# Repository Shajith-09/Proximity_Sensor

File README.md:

View this project on [CADLAB.io](https://cadlab.io/project/29333). 

# Proximity_Sensor

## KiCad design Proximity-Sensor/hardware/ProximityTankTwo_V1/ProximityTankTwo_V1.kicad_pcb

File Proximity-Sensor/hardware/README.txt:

cristinel.ababei, 2020

These are KiCad complete projects for:

--Base board
ProximityMother_V1/

--Single LC tank, 7 turns
ProximityTankOne_Square7Turns/

--Dual LC tank, 14 turns each
ProximityTankTwo_V1/

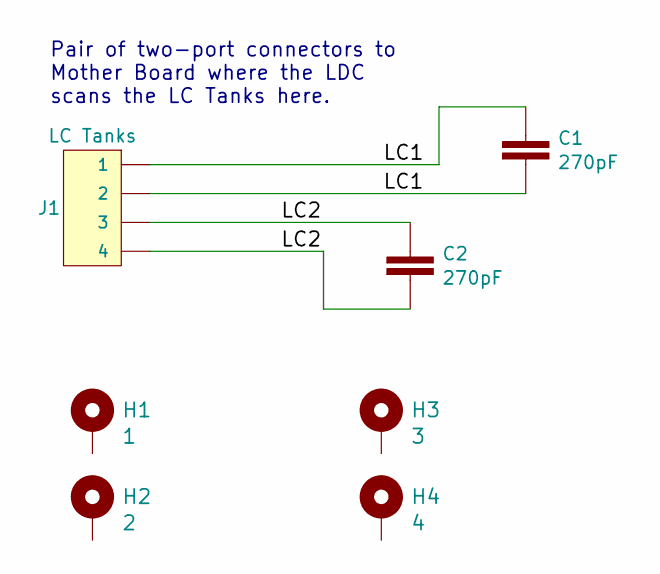
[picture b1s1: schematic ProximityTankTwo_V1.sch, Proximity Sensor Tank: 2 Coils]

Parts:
C1, C2: 270pF; C_0805_2012Metric_Pad1.15x1.40mm_HandSolder
H1: 1; STANDOFF_GROUNDING
H2: 2; STANDOFF_GROUNDING
H3: 3; STANDOFF_GROUNDING
H4: 4; STANDOFF_GROUNDING
J1: LC Tanks; 1X04

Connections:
/LC1: C1.1, C1.2, J1.1, J1.2
/LC2: C2.1, C2.2, J1.3, J1.4

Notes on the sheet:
Pair of two-port connectors to Mother Board where the LDC scans the LC Tanks here.

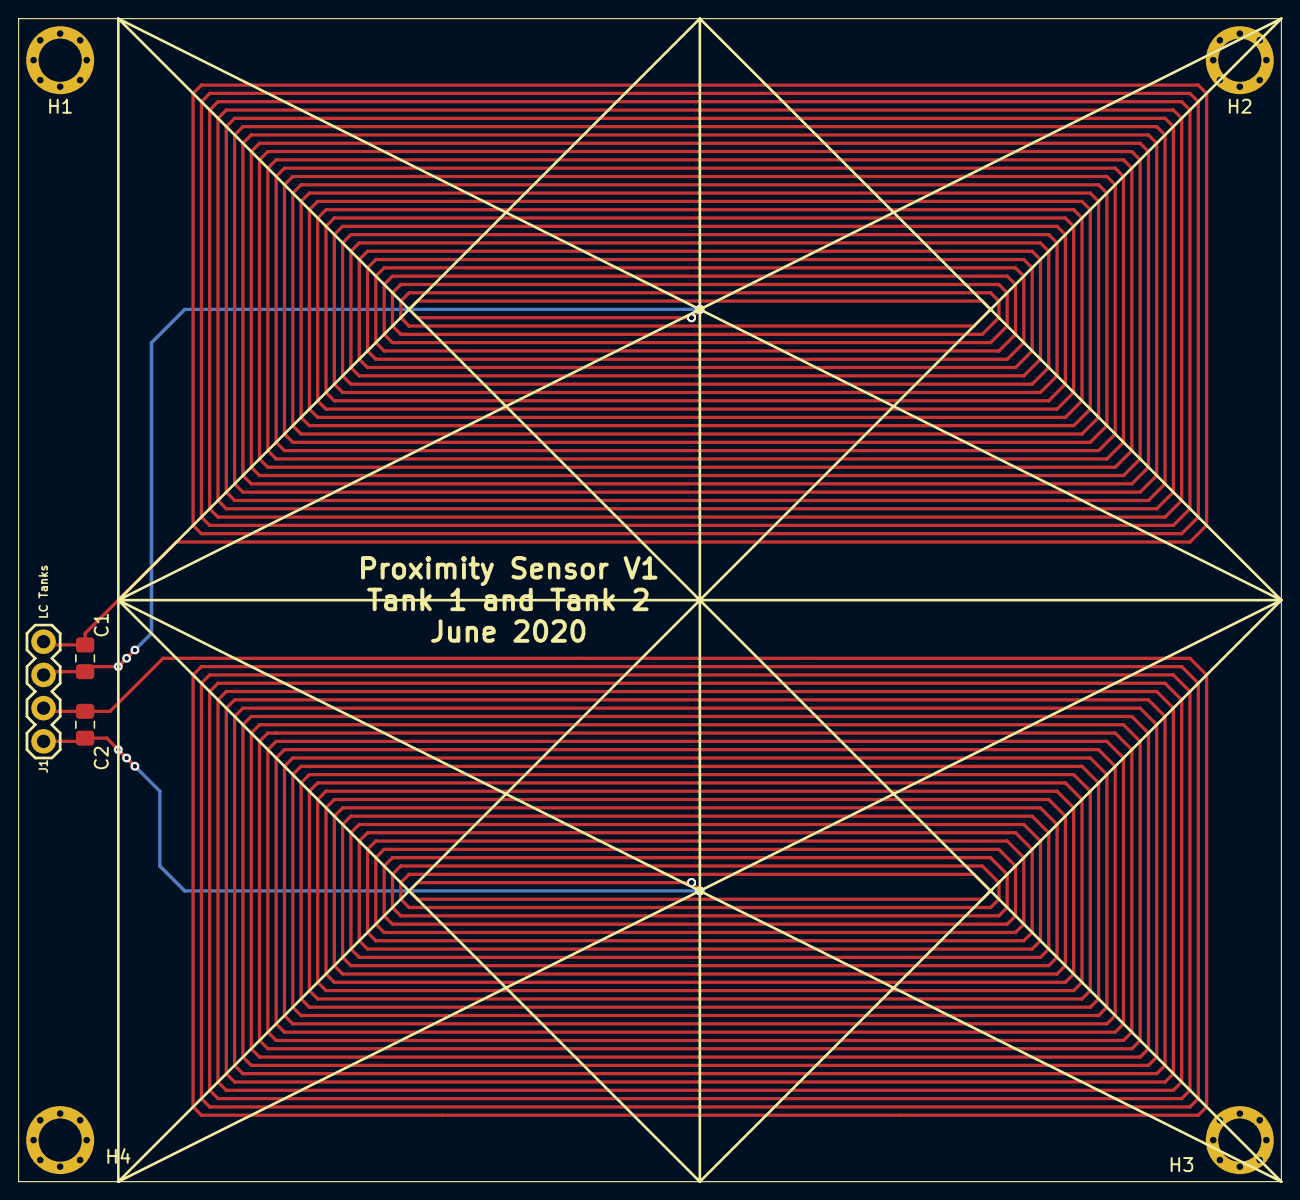
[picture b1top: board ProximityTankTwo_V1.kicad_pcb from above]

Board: 2 copper layers, 7 parts (0 on the bottom side), 2 nets.

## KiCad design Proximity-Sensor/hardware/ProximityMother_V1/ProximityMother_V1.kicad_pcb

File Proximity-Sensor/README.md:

cristinel.ababei, 2021 

Project: Proximity Sensor Design

--Description: 
This is a plug-and-play printed circuit board (PCB) proximity sensor design. It detects metal targets approaching perpendicularly as well as their moving direction. It uses an inductance to digital converter circuit. Machine learning models are used to differentiate between different types of metals (in V2 only). All HW and SW source files are included. HW includes PCB layout files in KiCad and SW includes firmware for the microcontroller (Atmega328p). 

--Short video domonstration: 
https://youtu.be/9pmw1QUPN_U

--More details in conference paper:
[1] Cristinel Ababei and James E. Richie, Sensor Design for Inductive Proximity and Moving Direction Sensing of Metal Targets, IEEE Int. Conf. on Modern Circuits and Systems Technologies (MOCAST), Thessaloniki, Greece, July 2021.

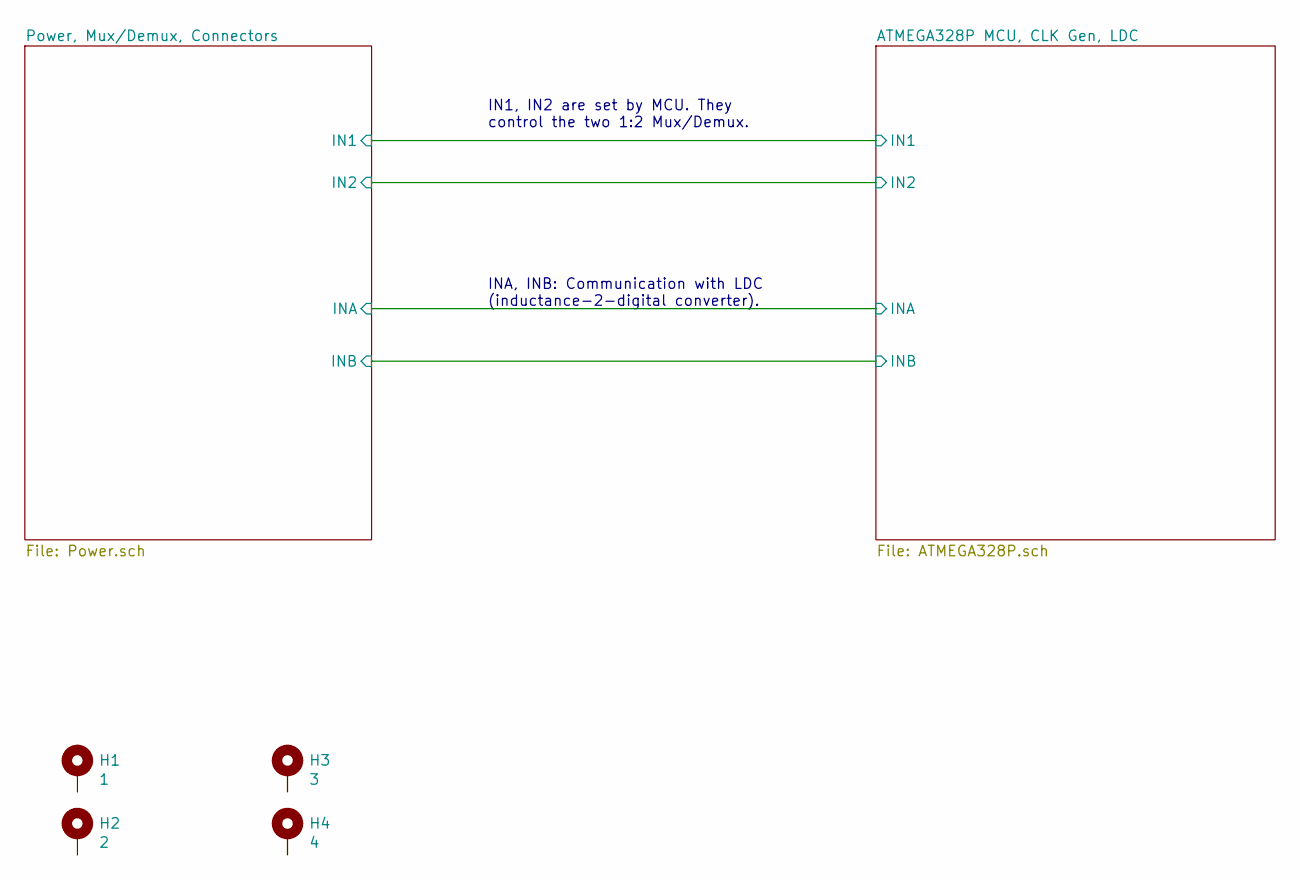
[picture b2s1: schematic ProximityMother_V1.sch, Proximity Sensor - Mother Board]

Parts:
H1: 1; STANDOFF_GROUNDING
H2: 2; STANDOFF_GROUNDING
H3: 3; STANDOFF_GROUNDING
H4: 4; STANDOFF_GROUNDING

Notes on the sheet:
IN1, IN2 are set by MCU. They control the two 1:2 Mux/Demux.
INA, INB: Communication with LDC (inductance-2-digital converter).

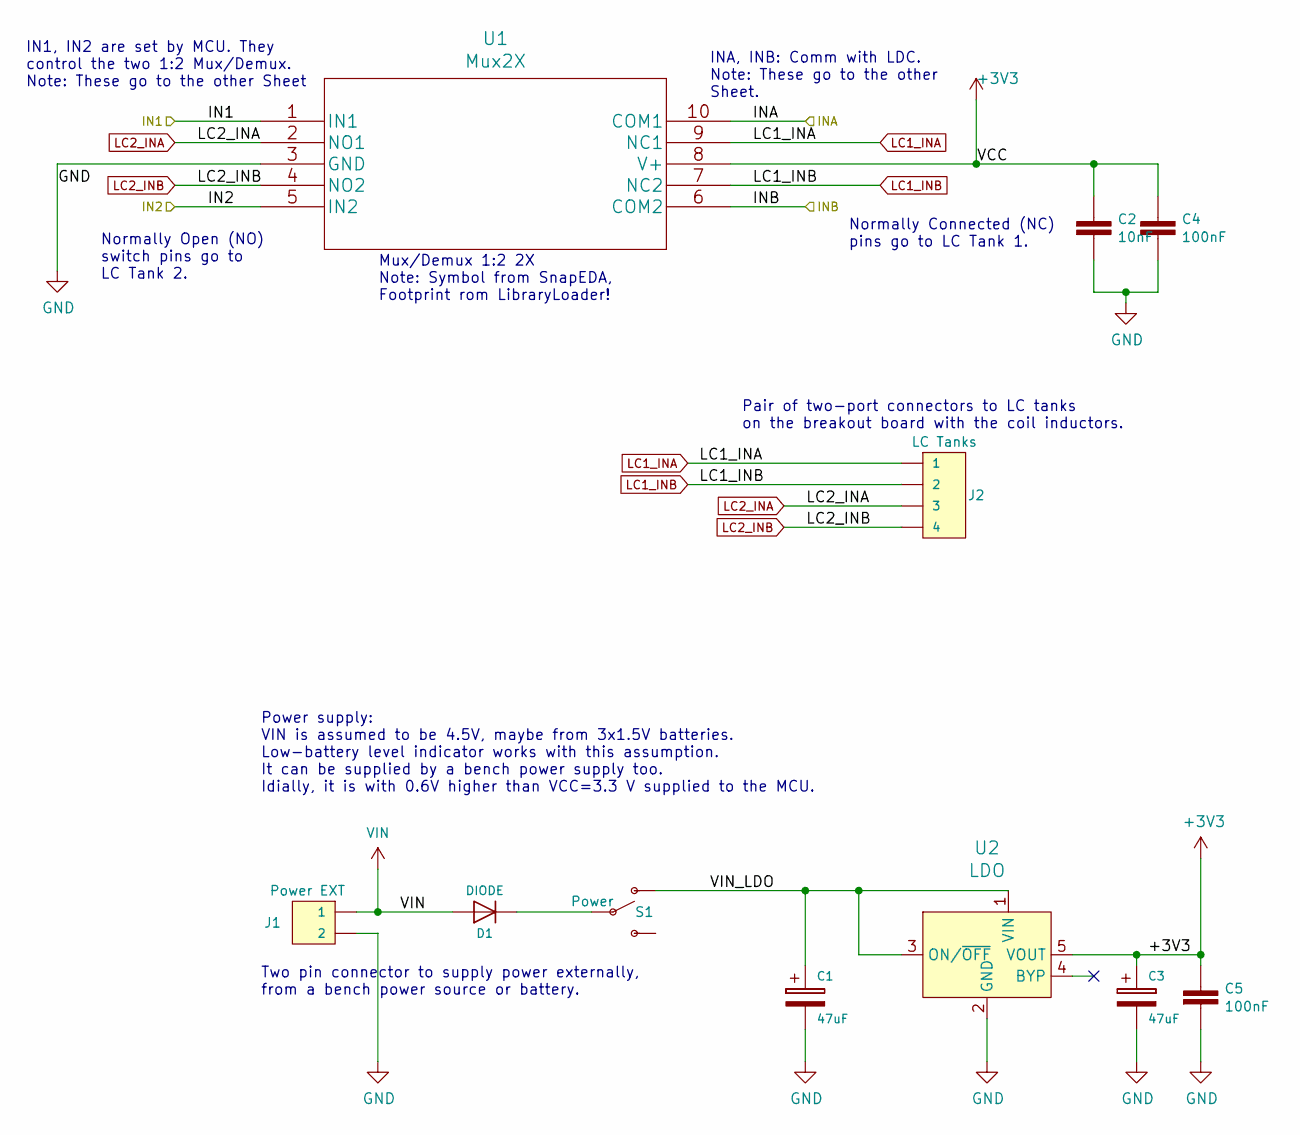
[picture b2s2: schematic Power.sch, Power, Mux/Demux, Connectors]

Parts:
C1, C3: 47uF; CP_Elec_5x4.5
C2: 10nF; C_1210_3225Metric_Pad1.42x2.65mm_HandSolder
C4, C5: 100nF; C_1210_3225Metric_Pad1.42x2.65mm_HandSolder
D1: DIODE; D_SOD-323_HandSoldering
J1: Power EXT; 1X02
J2: LC Tanks; 1X04
S1: Power; SWITCH_SPDT_PTH_11.6X4.0MM
U1: Mux2X; SOP50P490X110-10N
U2: LDO; SOT-753; MPN LP2985-33DBVR; Digi-Key_PN 296-18476-1-ND

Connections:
+3V3: C2.1, C3.1, C4.1, C5.1, U1.8 (V+), U2.5 (VOUT); also elsewhere on the board
/ATMEGA328P MCU, CLK Gen, LDC/INA: U1.10 (COM1); also elsewhere on the board
/ATMEGA328P MCU, CLK Gen, LDC/INB: U1.6 (COM2); also elsewhere on the board
/Power, Mux/Demux, Connectors/VIN_LDO: C1.1, S1.1 (O), U2.1 (VIN), U2.3 (ON/~OFF)
CTRL_MUX12: U1.1 (IN1), U1.5 (IN2); also elsewhere on the board
GND: C1.2, C2.2, C3.2, C4.2, C5.2, J1.2, U1.3 (GND), U2.2 (GND); also elsewhere on the board
LC1_INA: J2.1, U1.9 (NC1)
LC1_INB: J2.2, U1.7 (NC2)
LC2_INA: J2.3, U1.2 (NO1)
LC2_INB: J2.4, U1.4 (NO2)
unnamed: D1.1 (K), S1.2
VIN: D1.2 (A), J1.1; also elsewhere on the board

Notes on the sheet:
Power supply: VIN is assumed to be 4.5V, maybe from 3x1.5V batteries. Low-battery level indicator works with this assumption. It can be supplied by a bench power supply too. Idially, it is with 0.6V higher than VCC=3.3 V supplied to the MCU.
Two pin connector to supply power externally, from a bench power source or battery.
Mux/Demux 1:2 2X Note: Symbol from SnapEDA, Footprint rom LibraryLoader!
INA, INB: Comm with LDC. Note: These go to the other Sheet.
IN1, IN2 are set by MCU. They control the two 1:2 Mux/Demux. Note: These go to the other Sheet
Pair of two-port connectors to LC tanks on the breakout board with the coil inductors.
Normally Connected (NC) pins go to LC Tank 1.
Normally Open (NO) switch pins go to LC Tank 2.

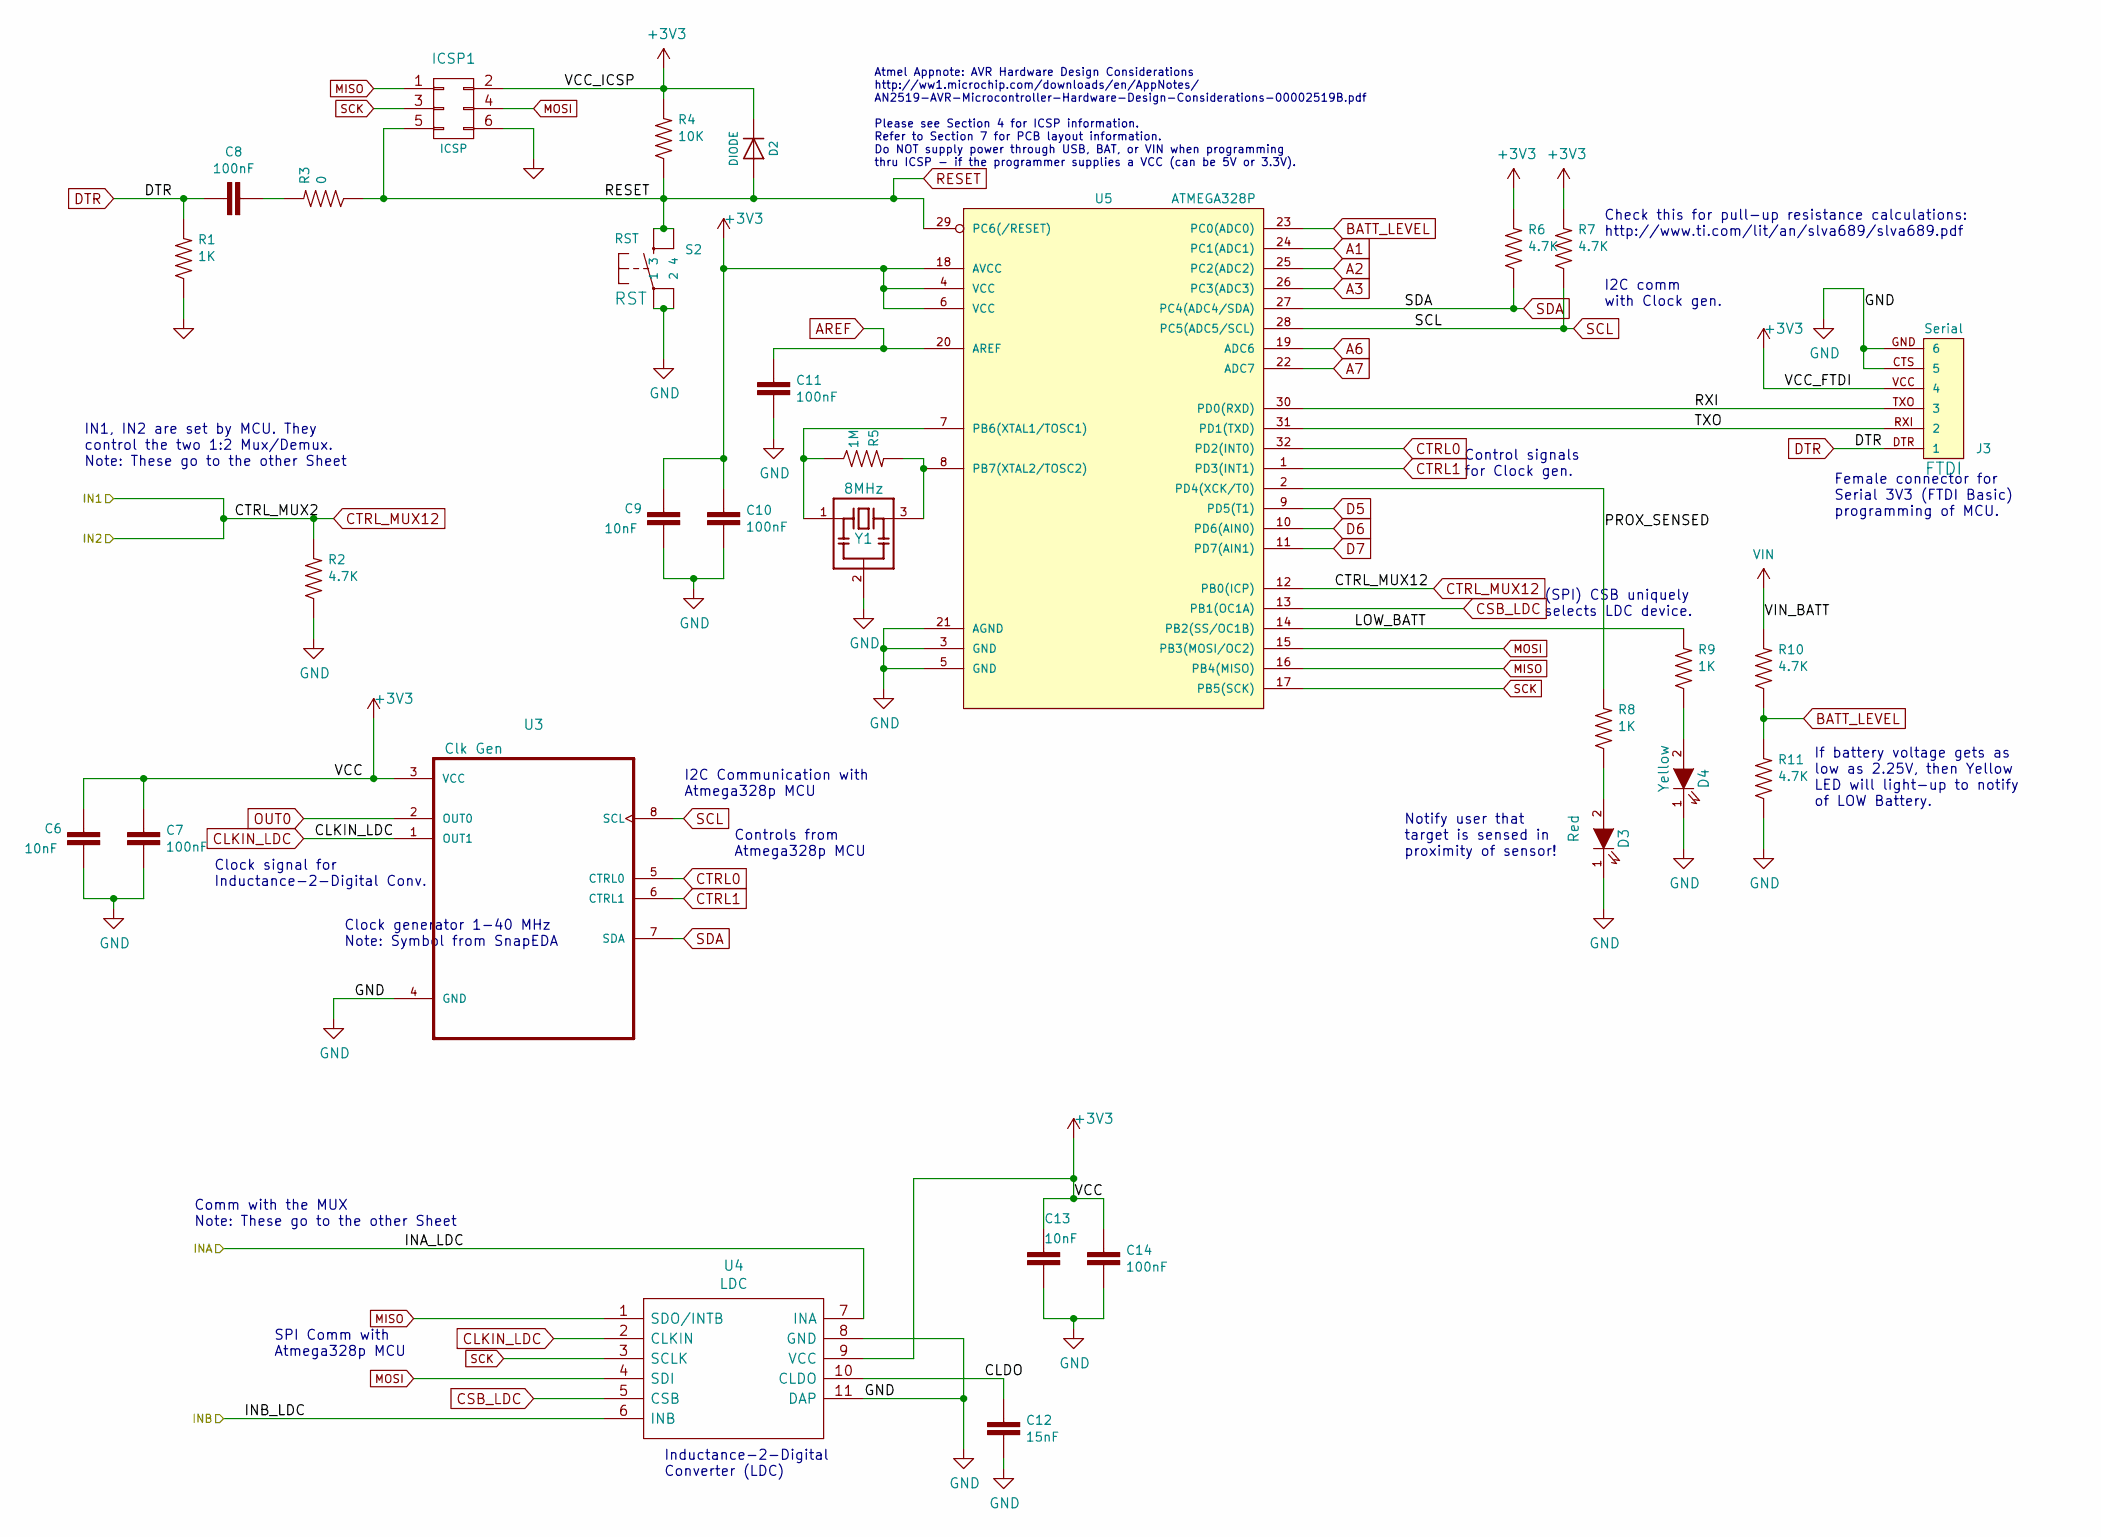
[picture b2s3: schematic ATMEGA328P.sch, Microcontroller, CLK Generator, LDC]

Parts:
C6, C9, C13: 10nF; C_1210_3225Metric_Pad1.42x2.65mm_HandSolder
C7, C8, C10, C11, C14: 100nF; C_1210_3225Metric_Pad1.42x2.65mm_HandSolder
C12: 15nF; C_1210_3225Metric_Pad1.42x2.65mm_HandSolder
D2: DIODE; D_SOD-323_HandSoldering
D3: Red; LED_1206_3216Metric
D4: Yellow; LED_1206_3216Metric
ICSP1: ICSP; 2X3
J3: Serial; FTDI_BASIC
R1, R8, R9: 1K; R_1210_3225Metric_Pad1.42x2.65mm_HandSolder
R2, R6, R7, R10, R11: 4.7K; R_1210_3225Metric_Pad1.42x2.65mm_HandSolder
R3: 0; R_1210_3225Metric_Pad1.42x2.65mm_HandSolder
R4: 10K; R_0805_2012Metric_Pad1.15x1.40mm_HandSolder
R5: 1M; R_1210_3225Metric_Pad1.42x2.65mm_HandSolder
S2: RST; TL3305AF160QG
U3: Clk Gen; SOIC127P600X175-8N
U4: LDC; TPS74901DRCR; Mouser Part Number 595-LDC1101DRCR
U5: ATMEGA328P; TQFP32-08
Y1: 8MHz; CSTNE8M00G55A000R0

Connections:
+3V3: C6.1, C7.1, C9.1, C10.1, C13.1, C14.1, D2.1 (K), ICSP1.2, J3.VCC (4), R4.2, R6.2, R7.2, U3.3 (VCC), U4.9 (VCC), U5.4 (VCC), U5.6 (VCC), U5.18 (AVCC); also elsewhere on the board
/ATMEGA328P MCU, CLK Gen, LDC/INA: U4.7 (INA); also elsewhere on the board
/ATMEGA328P MCU, CLK Gen, LDC/INB: U4.6 (INB); also elsewhere on the board
/ATMEGA328P MCU, CLK Gen, LDC/LOW_BATT: R9.2, U5.14 (PB2(SS/OC1B))
/ATMEGA328P MCU, CLK Gen, LDC/PROX_SENSED: R8.2, U5.2 (PD4(XCK/T0))
/ATMEGA328P MCU, CLK Gen, LDC/RXI: J3.TXO (3), U5.30 (PD0(RXD))
/ATMEGA328P MCU, CLK Gen, LDC/TXO: J3.RXI (2), U5.31 (PD1(TXD))
A1: U5.24 (PC1(ADC1))
A2: U5.25 (PC2(ADC2))
A3: U5.26 (PC3(ADC3))
A6: U5.19 (ADC6)
A7: U5.22 (ADC7)
AREF: C11.2, U5.20 (AREF)
BATT_LEVEL: R10.1, R11.2, U5.23 (PC0(ADC0))
CLKIN_LDC: U3.1 (OUT1), U4.2 (CLKIN)
CSB_LDC: U4.5 (CSB), U5.13 (PB1(OC1A))
CTRL0: U3.5 (CTRL0), U5.32 (PD2(INT0))
CTRL1: U3.6 (CTRL1), U5.1 (PD3(INT1))
CTRL_MUX12: R2.2, U5.12 (PB0(ICP)); also elsewhere on the board
D5: U5.9 (PD5(T1))
D6: U5.10 (PD6(AIN0))
D7: U5.11 (PD7(AIN1))
DTR: C8.1, J3.DTR (1), R1.2
GND: C6.2, C7.2, C9.2, C10.2, C11.1, C12.1, C13.2, C14.2, D3.1 (K), D4.1 (K), ICSP1.6, J3.CTS (5), J3.GND (6), R1.1, R2.1, R11.1, S2.1, S2.2, U3.4 (GND), U4.8 (GND), U4.11 (DAP), U5.3 (GND), U5.5 (GND), U5.21 (AGND), Y1.2; also elsewhere on the board
MISO: ICSP1.1, U4.1 (SDO/INTB), U5.16 (PB4(MISO))
MOSI: ICSP1.4, U4.4 (SDI), U5.15 (PB3(MOSI/OC2))
unnamed: C8.2, R3.2
unnamed: C12.2, U4.10 (CLDO)
unnamed: D3.2 (A), R8.1
unnamed: D4.2 (A), R9.1
unnamed: R5.1, U5.7 (PB6(XTAL1/TOSC1)), Y1.1
unnamed: R5.2, U5.8 (PB7(XTAL2/TOSC2)), Y1.3
OUT0: U3.2 (OUT0)
RESET: D2.2 (A), ICSP1.5, R3.1, R4.1, S2.3, S2.4, U5.29 (PC6(/RESET))
SCK: ICSP1.3, U4.3 (SCLK), U5.17 (PB5(SCK))
SCL: R7.1, U3.8 (SCL), U5.28 (PC5(ADC5/SCL))
SDA: R6.1, U3.7 (SDA), U5.27 (PC4(ADC4/SDA))
VIN: R10.2; also elsewhere on the board

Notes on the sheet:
Atmel Appnote: AVR Hardware Design Considerations http://ww1.microchip.com/downloads/en/AppNotes/ AN2519-AVR-Microcontroller-Hardware-Design-Considerations-00002519B.pdf Please see Section 4 for ICSP information. Refer to Section 7 for PCB layout information. Do NOT supply power through USB, BAT, o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
Control signals for Clock gen.
Check this for pull-up resistance calculations: http://www.ti.com/lit/an/slva689/slva689.pdf
If battery voltage gets as low as 2.25V, then Yellow LED will light-up to notify of LOW Battery.
Female connector for Serial 3V3 (FTDI Basic) programming of MCU.
Inductance-2-Digital Converter (LDC)
Clock generator 1-40 MHz Note: Symbol from SnapEDA
I2C Communication with Atmega328p MCU
Clock signal for Inductance-2-Digital Conv.
I2C comm with Clock gen.
Controls from Atmega328p MCU
Comm with the MUX Note: These go to the other Sheet
IN1, IN2 are set by MCU. They control the two 1:2 Mux/Demux. Note: These go to the other Sheet
(SPI) CSB uniquely selects LDC device.
Notify user that target is sensed in proximity of sensor!
SPI Comm with Atmega328p MCU

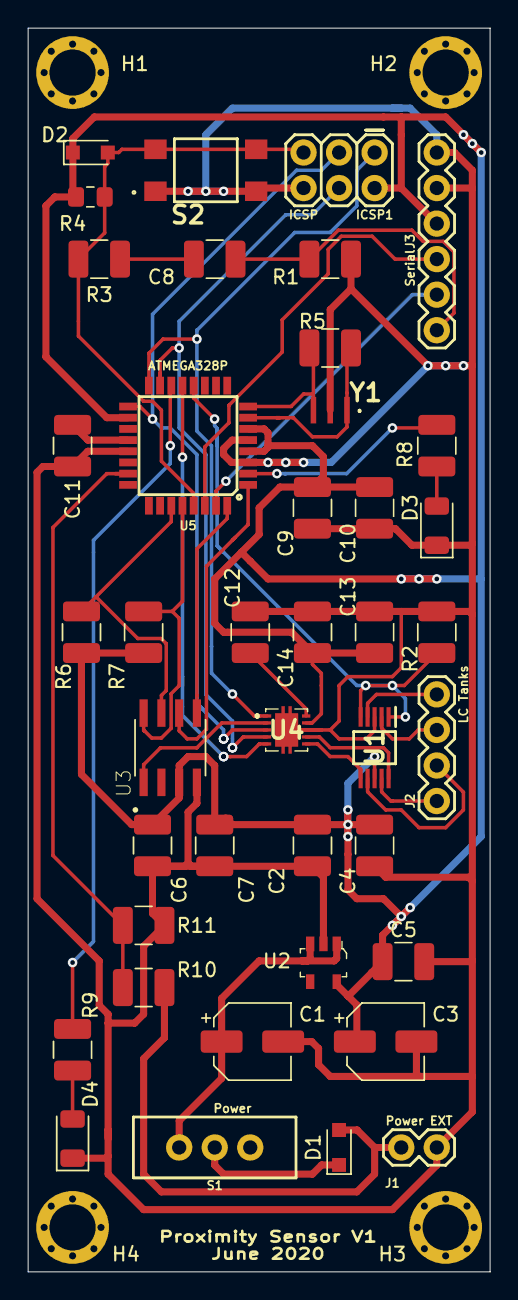
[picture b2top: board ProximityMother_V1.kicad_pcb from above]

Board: 2 copper layers, 33.0 x 88.9 mm, 45 parts (0 on the bottom side), 35 nets.

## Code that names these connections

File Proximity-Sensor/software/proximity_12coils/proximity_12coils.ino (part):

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//
// In the ProximityBoard design I made the mistake to use the SS pin of 
// the SPI peripheral as battery low pin to drive an LED; and, instead
// I used PB1 as a pin with the function of slave select to use to 
// connect to the LDC; I should have used these two pins swapped! will do next time;
// for now, I need to replacce the IDE pin SS with PB1 (IDE pin 9) so that the LDC
// will be selected correctly as a Slave chip, by the MCU Atmega328p the master;
//
// That is why I duplicated the SPIClass which is the type-of that the SPI object
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  Serial.print("Check status of inductance to digital converter: LDC1101... \r\n");
  query_LDC1101_device_during_setup( DEBUG);

  // the MCU pin 2 (or PD4), which is IDE pin 4 drives the RED LED to
  // signal that metal target entered the sensor's vicinity;
  // so, set this pin as out here; 
  pinMode(4, OUTPUT);
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  
  // () configure the MUX to connect tank LC2 to the inductance-to-digital converter;
  // the MUX is the "TS5A23157 Dual 10-Ω SPDT Analog Switch" IC, which
  // I control with PB0 (IDE pin 8, also MCU pin 12); 
  // to control the MUX to select LC2 (i.e., LC2_INA and LC2_INB) I need to set the control pin HIGH;
  Serial.print("********************************************************* \r\n");
  Serial.print("Configure MUX: TS5A23157 Dual 10-Ω SPDT Analog Switch... \r\n");
  pinMode(8, OUTPUT);
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  // into LDC1101;
  
  // (1) set CTRL0 and CTRL1 of the clock generator to 0; reccommended;
  // these are connected to PD2 and PD3 of the Atmega328p MCU in teh ProximityBoard;
  // that is Arduino IDE pins 2 and 3;
  pinMode(2, OUTPUT);
  digitalWrite(2, LOW);
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  
  // (1) configure the MUX to connect tank LC2 to the inductance-to-digital converter;
  // the MUX is the "TS5A23157 Dual 10-Ω SPDT Analog Switch" IC, which
  // I control with PB0 (IDE pin 8, also MCU pin 12); 
  // to control the MUX to select LC2 (i.e., LC2_INA and LC2_INB) I need to set the control pin HIGH;
  digitalWrite(8, HIGH); 
  // ----------     ----------
  //           | --|
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  // is connected to the base board;
  // used just for metal target detection approaching perpendicularly    

  // (1) MUX to select LC2 (i.e., LC2_INA and LC2_INB) I need to set the control pin HIGH;
  digitalWrite(8, HIGH);
  
  
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  // LC1 then LC2 == LEFT TO RIGHT
 
  
  // (1) control the MUX to select LC2 (i.e., LC2_INA and LC2_INB) I need to set the control pin HIGH;
  digitalWrite(8, HIGH); 

  
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  // LC1 then LC2 == LEFT TO RIGHT
 

  // (1) control the MUX to select LC1 (i.e., LC1_INA and LC1_INB) I need to set the control pin LOW;
  digitalWrite(8, LOW); 
 
  
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
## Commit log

2025-04-29 Backlink to CADLAB.io has been added.

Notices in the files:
Proximity-Sensor/software/proximity_12coils/proximity_12coils.ino:
cristinel.ababei, jim.richie, copyleft :-), october 2020
